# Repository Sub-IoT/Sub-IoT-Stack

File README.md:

# WARNING: THIS REPOSITORY IS NOT ACTIVELY MAINTAINED ANYMORE

# Welcome

Sub-IoT houses an implementation of the [DASH 7 Alliance](http://www.dash7-alliance.org) protocol, which can be optionally combined with a 3rd party implementation [LoRaMAC-node](https://github.com/Lora-net/LoRaMac-node) of the [LoRaWAN](https://lora-alliance.org/) specification for ultra low power communication. The aim of the project is to provide an implementation of the sub-GHz stacks which allows for fast development and prototyping. This implementation focusses on completeness, correctness, ease of use and understanding. Performance and code size are less important aspects. For clarity a clear separation between the ISO layers is maintained in the code.

For more information visit the [Sub-IoT site](https://sub-iot.github.io/Sub-IoT-Stack/).

# Getting Started

Please refer to the [documentation section on our site](https://sub-iot.github.io/Sub-IoT-Stack/docs/home/).

# Related repositories

[pyd7a](https://github.com/Sub-IoT/pyd7a) provides a collection of python modules, supporting the DASH7 Alliance Protocol in general, and Sub-IoT in particular.

# Community

The developers can be reached on the [dash7-ap-oss Google Group](https://groups.google.com/forum/#!forum/dash7-ap-oss)

# License

Licensed under the Apache License, Version 2.0 (the "License"): You may not use these files except in compliance with the License. You may obtain a copy of the License at [http://www.apache.org/licenses/LICENSE-2.0](http://www.apache.org/licenses/LICENSE-2.0)

Unless required by applicable law or agreed to in writing, software distributed under the License is distributed on an "AS IS" BASIS, WITHOUT WARRANTIES OR CONDITIONS OF ANY KIND, either express or implied. See the License for the specific language governing permissions and limitations under the License.

&copy; Copyright 2015-2021, University of Antwerp, Aloxy NV and others

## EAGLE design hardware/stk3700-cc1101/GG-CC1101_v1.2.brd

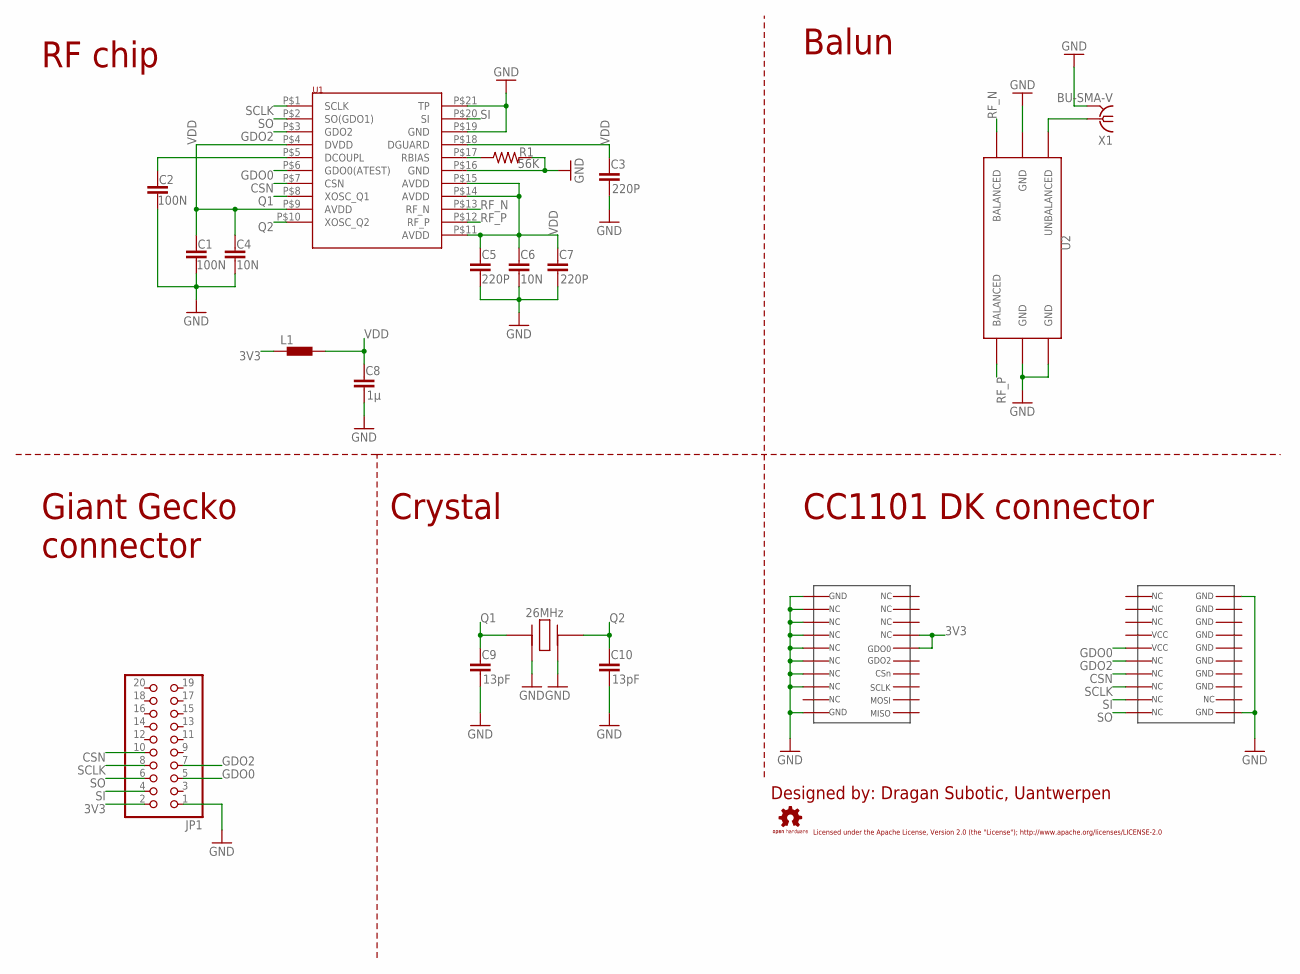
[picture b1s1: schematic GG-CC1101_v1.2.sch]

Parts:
C1, C2: 100N; 0805
C3, C5, C7: 220P; 0805
C4, C6: 10N; 0805
C8: 1µ; 0805
C9, C10: 13pF; 0805
JP1: PINHD-2X10; 2X10
L1: BLM15HG102SN1; 0402
Q1: XTAL-26MHZ
R1: 56K; 0805
U1: CC1101
U2: BALUN-433MHZ
U$1: CC1101-EVAL_KIT
X1: BU-SMA-V

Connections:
3V3: JP1.2, L1.1, U$1.P$14, U$1.P$15
CSN: JP1.10, U1.P$7 (CSN), U$1.P$24
GDO0: JP1.5, U1.P$6 (GDO0(ATEST)), U$1.P$26
GDO2: JP1.7, U1.P$3 (GDO2), U$1.P$25
GND: C1.2, C2.2, C3.2, C4.2, C5.2, C6.2, C7.2, C8.2, C9.2, C10.2, JP1.1, Q1.P$2, Q1.P$4, R1.2, U1.P$16 (GND), U1.P$19 (GND), U1.P$21 (TP), U2.P$2 (GND), U2.P$5 (GND), U2.P$6 (GND), U$1.P$1, U$1.P$3, U$1.P$4, U$1.P$5, U$1.P$6, U$1.P$7, U$1.P$8, U$1.P$9, U$1.P$10, U$1.P$31, U$1.P$40, X1.2, X1.3 (2), X1.4 (2), X1.5 (2)
unnamed: C2.1, U1.P$5 (DCOUPL)
unnamed: R1.1, U1.P$17 (RBIAS)
unnamed: U2.P$1 (UNBALANCED), X1.1
Q1: C9.1, Q1.P$1, U1.P$8 (XOSC_Q1)
Q2: C10.1, Q1.P$3, U1.P$10 (XOSC_Q2)
RF_N: U1.P$13 (RF_N), U2.P$3 (BALANCED)
RF_P: U1.P$12 (RF_P), U2.P$4 (BALANCED)
SCLK: JP1.8, U1.P$1 (SCLK), U$1.P$23
SI: JP1.4, U1.P$20 (SI), U$1.P$22
SO: JP1.6, U1.P$2 (SO(GDO1)), U$1.P$21
VDD: C1.1, C3.1, C4.1, C5.1, C6.1, C7.1, C8.1, L1.2, U1.P$4 (DVDD), U1.P$9 (AVDD), U1.P$11 (AVDD), U1.P$14 (AVDD), U1.P$15 (AVDD), U1.P$18 (DGUARD)

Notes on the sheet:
RF chip
Balun
Giant Gecko connector
CC1101 DK connector
Crystal
26MHz
Designed by: Dragan Subotic, Uantwerpen
Licensed under the Apache License, Version 2.0 (the "License"); http://www.apache.org/licenses/LICENSE-2.0

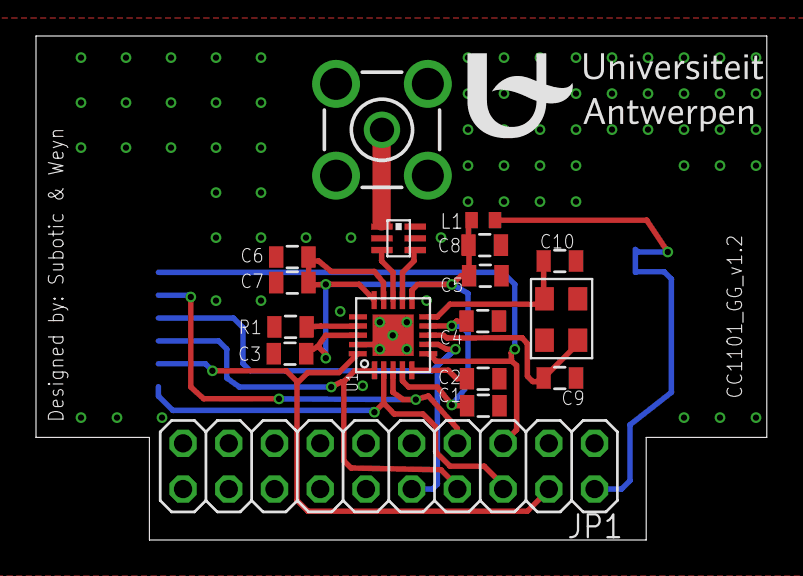
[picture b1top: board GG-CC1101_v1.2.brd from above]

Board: 2 copper layers, 40.6 x 28.0 mm, 18 parts (1 on the bottom side), 16 nets.

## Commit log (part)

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2020-08-14 make it possible to unregister a handler, add modem_restart function
2020-08-14 applied feedback, applied formatting
2020-08-19 set cmake-settings
2020-08-24 now enable NLS by default
2020-08-24 still very much WIP, temporary commit
2020-08-27 bugfix in write-file
2020-08-27 added START and STOP alp OP, make possible to call from oss7-modem, create file in alp layer that keeps last active interface, make sure interfaces can be (de)inited multiple times
2020-08-27 active stack now gets set in d7ap_fs_data, fixed bug that caused no clients to register for answers, added logging option
2020-08-27 fix flawed logic in d7ap_interface, d7ap init now also registers the client for d7
2020-08-27 blockdevice_erase_sector4k() wrongly called erase_block32k()
2020-08-27 increase default permanent storage size
2020-08-27 updated platforms to new blockdevice definition
2020-08-27 AL-925: Merge AL-925-enable-encryption-using-hw to AL-830-avoid-modem-firmware-resets
2020-08-27 add location for wolfboot version
2020-08-27 adapted other stm32 based platforms to set FLASH_ORIGIN and FLASH_LENGTH in cmake
2020-08-27 fix NUCLEO_L073RZ linker script filename
2020-08-27 query fix, change alp-parse-length
2020-08-27 Add ability to register custom block devices to the file system
    * Fixed incorrect address while registering a new permanent file.
    * Volatile files aren't kept in permanent memory anymore
    * fs_init_file now uses bd_types instead of storage classes
2020-08-27 Add check to see if block device exists before reading/writing to files
2020-08-27 length bugfix
2020-08-27 enable building a relocated binary for using on top of a bootloader + adapted B_L072Z_LRWAN1 platform
2020-08-27 if initial data is empty, a create file will not use a buffer of the entire length of the file but only the occupied part
2020-08-27 blockdevice now indicates write/erase block size, init file will use this
2020-08-31 AL-949: Merge AL-949-alp_layer-doesnt-seem-to-return-an-interface-status-from-an-unsollicited-response-to-the-application-itf to master
2020-09-02 STM32L0 LPTIM bugfix: timer fires early
    The STM32L0 LPTIM peripheral appears to trigger a match interrupt
    whenever LPTIM_CMP >= LPTIM_CNT. Not only of LPTIM_CMP == LPTIM_CNT.
    In most cases this works just fine: a timer interrupt is scheduled for t_future > t_now.
    As soon as the counter hits t_future, the interrupt is raised as
    expected.
    However, this timer is just 16-bits, overflowing every 64 seconds
2020-09-04 possibility to set maxfilesize array as cmake variable
2020-09-04 changed error code type
2020-09-29 cancel the previous timer before waiting for overflow
2020-10-05 deinit radio io in lorawan driver
2020-10-13 AL-1011: Merge AL-1011-create-access-profiles-for-us to master
2020-10-20 support DMA for SPI
2020-10-22 Bugfix: long tasks may fire too early depending on previous task
    If scheduling a long delay (lets say 300 seconds, >> 1 16-bit
    overflow) while another task is already schedules, the timer stays
    programmed for the first timeout, causing the second task to fire early
2020-11-02 d7ap_fs: use D7AP stack logging rather than NWL. Add missing logging enable cmake option. phy: some defensive programming changes to prevent possible divide by zero and stack overrun. serial_interfac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
2020-11-13 Al 1141 global fixes
2020-12-02 reverse enabled logic
2020-12-10 check if cmp_reg_write_pending before going to sleep so that we don't wake up immediately after going to sleep
2021-01-06 take hw timer overflow of task time + current hw time into account in timer.c instead of in stm32_common_timer.c
    A fix was implemented for a task that would overflow because of the task time + current hw time in stm32 common timer. Some mechanism already existed in the layer above (timer.c). Since the fix in st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
2021-01-10 docs: fix spec link
2021-01-29 adjust error handling in lorawan interface and lorawan stack
2021-02-15 AL-1300: Merge AL-1300-d7atp-gateway-modem-should-signal-tag-thats-it-not-preferred to master
2021-02-16 AL-811: Merge AL-811-filesystem-permissions to master
2021-02-19 bugfix boolean error, once there was one alp error, all next responses on requests would return an error until reboot
2021-03-02 treat compiler warnings as errors
2021-03-03 fix Cortus build due to missing symbol regarding the d7ap_fs buffers
    The Attribute used is not sufficient to force the compiler to emit
    symbol for the d7ap_fs buffers. We need to modify the libraries build ordering
2021-03-03 fs: fix build when using default values like the PERMANENT_STORAGE_SIZE
2021-03-03 fs: fix warnings
2021-03-03 alp_layer: free resp_command in case of unregistered interface
2021-03-03 d7asp: fix bitmap search size
2021-03-03 d7atp: fix start and Tl flag in D7ATP ctrl header
2021-03-03 d7a: registration is only possible when the stack is completly initialised
2021-03-03 d7asp: remove alp payload terminology
2021-03-03 d7asp: set TX duration for each request (used by TL computation)
2021-03-03 crc: extend crc computation to larger payloads
2021-03-05 add permission change in fs api, toggle key files permission using cmake
2021-04-30 AL-1534: Merge AL-1534-pulse-should-be-able-to-trigger-both-updates-sequentially-without-extra-interaction-of-the-smartphone to master
2021-05-26 fix bug in the way UID on STM32 is generated, we where reading bits of undefined memory by a wrong cast
2021-06-22 AL-1637-code-takes-pointer-from-pointer-where-it-should-just-take-the-original-pointer
2021-06-25 update-of-loramac-node-and-move-to-submodule
2021-07-08 AL-1692: Merge AL-1692-a-write-file-header-should-now-be-allowed-to-write-an-allocated-length-bigger-than-the-previous-allocated-length to master
2021-07-12 Bump addressable from 2.5.1 to 2.8.0 in /docs
    Bumps [addressable](https://github.com/sporkmonger/addressable) from 2.5.1 to 2.8.0.
    - [Release notes](https://github.com/sporkmonger/addressable/releases)
    - [Changelog](https://github.com/sporkmonger/addressable/blob/main/CHANGELOG.md)
    - [Commits](https://github.com/sporkmonger/addressable/compare/addressable-2.5.1...addressable-2.8.0)
    ---
    updated-dependencies:
2021-07-29 Updates LoRaMac-node to grab change which fixes issue where tag can be trying to join LoRaWAN while not in provisioning mode.
2021-08-06 retry init clock if failes
2021-08-18 add PLATFORM_NO_REBOOT_REASON_TRANSMIT to modem interface
2021-09-08 AL-1185: Merge AL-1185-uart-error-3 to master
2021-09-13 reset is_full flag on fifo_clear
2021-09-20 AL-1859 clean up examples and documentation
2021-09-20 There is a mismatch between the internal usage of the D7 session result and the expected result according to the stack This adapts the APIs so we can easily cast the result to the new struct
2021-09-27 add sensor push led example
2021-09-28 AL-1884-update-license-headers
2021-10-12 AL-1738: Fix verifying after programming of flash
2021-10-21 AL-1924: Merge AL-1924-rename-powerprofile-features to master
2021-10-25 improve error message so that it refers to the cmake variable name
2021-10-28 add ble interface
2021-10-28 forgot .h file
2021-10-28 AL-1663: Fix tests Addapt to changes done to SPI and I2C definitions
2021-11-03 Remove "aloxy" from .gitmodules.
2021-11-18 Add AS923 build by bumping LoRaWAN
2021-12-15 print error string when in atomic
2021-12-20 bugfix operand query
2021-12-20 Fix lorawan submodule points to an invalid commit
2021-12-22 periodic-timer-should-get-rescheduled-in-another-way
2022-02-21 AL-2305: Merge AL-2305-reset-of-modem_interface-during-transaction-causes-lock-up-of-modem_interface to master
2022-02-26 push7 platform fixes
2022-03-03 Little queue improvements (make generic, max retries, network timeout)
2022-03-05 add initial pir testcode
2022-03-16 AL-2387: Merge AL-2387-rx-of-modeminterface-can-block-by-incomplete-packet to master
2022-03-16 AL-2418: Merge AL-2418-timeout-variable-is-only-reset-on-timeout-but-not-when-action-succeeds to master
2022-03-22 AL-2433: Merge AL-2433-timer_get_counter_value-returns-wrong-value-when-overflow-occurs-during-execution-of-the-function to master
2022-03-25 AL-2465: Add CMake variable for duty cycle in AS923
2022-04-08 AL-2477: Merge AL-2477-create-persistent-error-file to master
2022-04-11 error event file: bugfix init, reset file on write, get last event as file
2022-04-12 AL-2502: Merge AL-2502-make-it-possible-to-create-a-stacktrace-in-the-timer-isr to master
2022-04-13 AL-2470: Error event file also logs assert event
2022-04-21 AL-2552: Merge AL-2552-scheduler-doesnt-compile-anymore-when-watchdog-is-disabled to master
2022-04-29 download all
2022-04-29 change env var by writing to GITHUB_ENV
2022-04-29 add extra output
2022-04-29 move env var up scope so all steps in run-testsuite can access
2022-04-29 access secret correctly
2022-04-29 don't apply clang-formatter at this time
2022-04-29 moving building stage to run on ubuntu-latest
2022-04-29 testing setting of env var
2022-04-29 also do lsof check before running testsuite
2022-05-02 add workflow_dispatch
2022-05-03 AL-2533: Fix cron time format
2022-05-10 Revert "Changes to enable and clean up C++ compilation:"
    This reverts commit baf2c98db79881a809167c4abc0af0a25b481bff.
2022-06-02 AL-2749: Merge AL-2749-move-flags-to-external-flash-on-modem-gateway to master
2022-06-10 added error exception for type-limits to fix bug with num_leds=0
2022-06-15 AL-2802: fix returned status when MAC commands get flushed over FPort 0
2022-08-09 apply changes to enable engineering mode for ANATEL testapp
2022-09-05 add assert to lorawan interface as it is not loaded when d7 is not included
2022-09-05 Apply changes required to support devnonce.
2022-09-06 EM-92: Merge EM-92-allow-a-task-to-be-scheduled-multiple-times to master
2022-09-09 EM-73: Merge EM-73-make-it-possible-to-make-multiple-instances-of-modem_interface-with-a-single-source-file to master
2022-10-24 try smaller packet queue size
2022-10-25 poc send unencrypted unauthenticated dormant session to other device through gateway
2022-11-10 sending-an-indirect-forward-on-an-unused-itf-resulted-in-fwd-over-host
2022-11-14 github-ci stores the highest common folder of the artifact paths
2022-12-08 Move module headers to their modules Clean-up dependencies
2022-12-09 EM-152: Define new common region enum
2023-01-03 EM-204: Merge EM-204-sched_check_software_watchdog-doesnt-return-a-value-if-watchdog-is-not-active to master
2023-02-21 enable reading out region from d7
2023-03-17 Bump lorawan
2023-04-28 Fixing yet another formatting error.
2023-04-28 Using different LoRaMac-node branch where functions don't exceed stack usage limits.
2023-04-28 Adding lorawan tests to stages, and restructuring new jobs.
2023-04-28 Adding LoRaWAN CI tests
2023-04-28 temporarily add no-check-certificate because arm's website's certs can't be verified.
2023-04-28 Temporarily performing shorter testsuite, for test purposes.
2023-04-28 Using CI_TOKEN to pull artifacts.
2023-04-28 specifically erase the DUT before setting up the gateway or flashing new version. This is to prevent frames from the old build being picked up by the gw and confusing the testsuite (because of the mi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
2023-04-28 Set the boolean variable for the final job the wrong way around...
2023-04-28 remove extra
2023-04-28 add docker image to lorawan build stage.
2023-04-28 adding debug info to flash-lorawan
2023-04-28 create build dir before entering.
2023-04-28 Move build location for LoRaWAN
2023-04-28 Separating out build and flash lorawan.
2023-04-28 Erase devkit after tests finish.
2023-04-28 Take deveui, appeui, gw_addr as gitlab variables.
2023-04-28 Removing curly braces around vars.
2023-04-28 Don't pull current-related results as the data download takes a very long time.
2023-04-28 Do not download current folder.
2023-05-31 EM-273: Update LoRaMac-node to v.4.7.0.
2023-06-15 EM-369: fix devnonce init and size.
2023-08-02 show ip address at start of gitlab job
2023-08-03 clarify comment
2024-03-27 add unknown alp interface ID
2024-05-23 EM-577: handle join request failure because of duty cycle limits
2024-10-07 EM-585: Add CN470 build

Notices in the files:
parts and their libraries:
SparkFun: Licensing: CC v3.0 Share-Alike You are welcome to use this library for commercial purposes.
